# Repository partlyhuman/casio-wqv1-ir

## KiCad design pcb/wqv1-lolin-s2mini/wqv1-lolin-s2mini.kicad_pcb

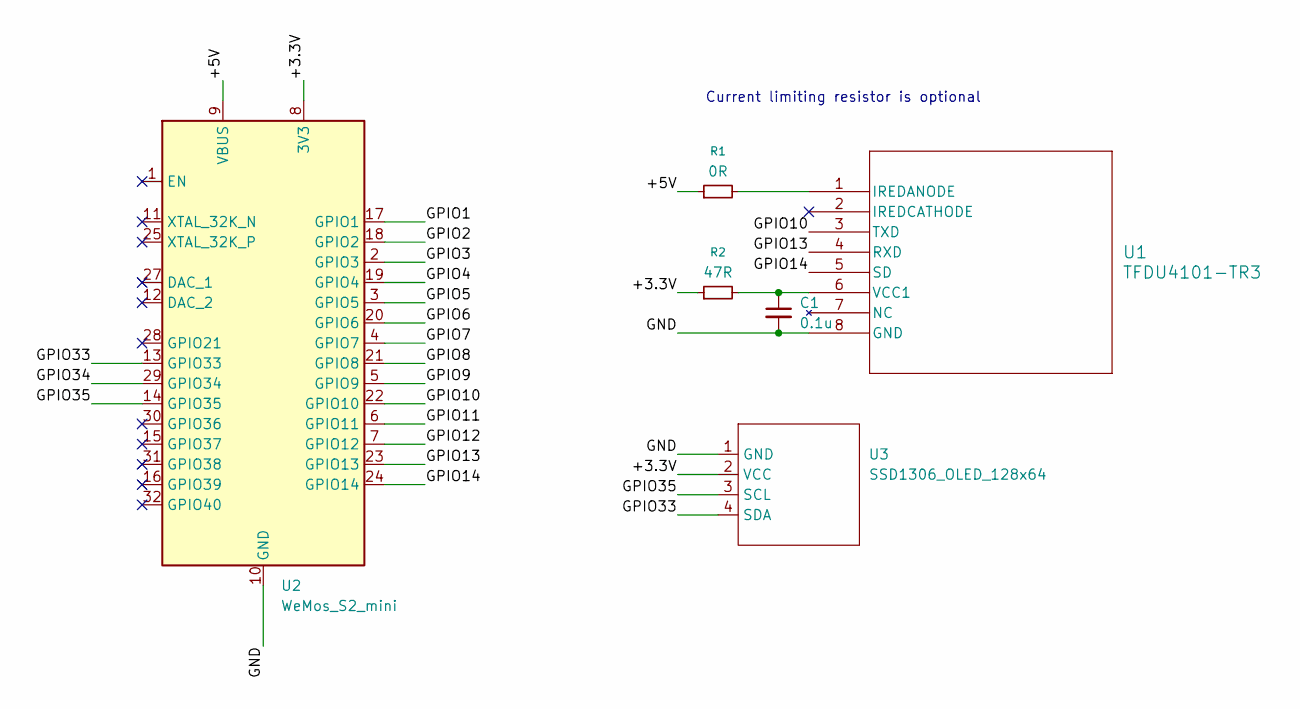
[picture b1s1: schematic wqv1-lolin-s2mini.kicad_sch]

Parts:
C1: 0.1u; C_0805_2012Metric_Pad1.18x1.45mm_HandSolder
R1: 0R; R_0805_2012Metric_Pad1.20x1.40mm_HandSolder
R2: 47R; R_0805_2012Metric_Pad1.20x1.40mm_HandSolder
U1: TFDU4101-TR3; SMT_101-TR3_VIS
U2: WeMos_S2_mini; WEMOS_S2_mini
U3: SSD1306_OLED_128x64; SSD1306

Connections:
/+3.3V: R2.1, U2.8 (3V3), U3.2 (VCC)
/+5V: R1.1, U2.9 (VBUS)
/GND: C1.2, U1.8 (GND), U2.10 (GND), U2.26 (GND), U3.1 (GND)
/GPIO1: U2.17 (GPIO1)
/GPIO2: U2.18 (GPIO2)
/GPIO3: U2.2 (GPIO3)
/GPIO4: U2.19 (GPIO4)
/GPIO5: U2.3 (GPIO5)
/GPIO6: U2.20 (GPIO6)
/GPIO7: U2.4 (GPIO7)
/GPIO8: U2.21 (GPIO8)
/GPIO9: U2.5 (GPIO9)
/GPIO10: U1.3 (TXD), U2.22 (GPIO10)
/GPIO11: U2.6 (GPIO11)
/GPIO12: U2.7 (GPIO12)
/GPIO13: U1.4 (RXD), U2.23 (GPIO13)
/GPIO14: U1.5 (SD), U2.24 (GPIO14)
/GPIO33: U2.13 (GPIO33), U3.4 (SDA)
/GPIO34: U2.29 (GPIO34)
/GPIO35: U2.14 (GPIO35), U3.3 (SCL)
unnamed: R1.2, U1.1 (IREDANODE)
unnamed: C1.1, R2.2, U1.6 (VCC1)

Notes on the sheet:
Current limiting resistor is optional

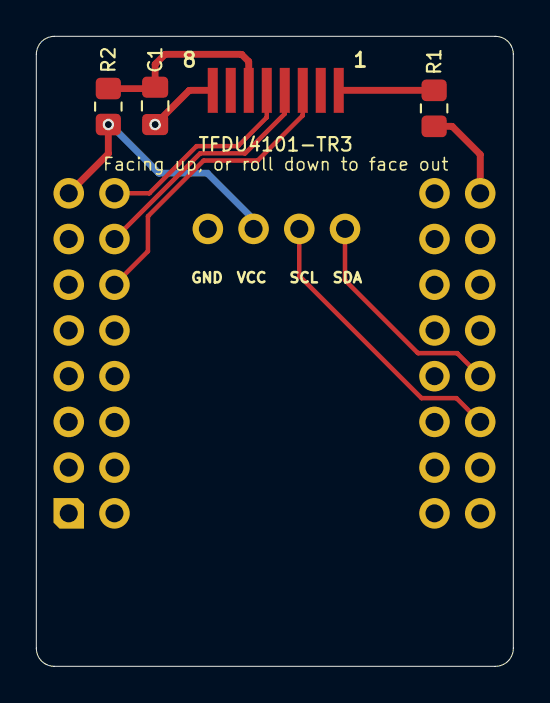
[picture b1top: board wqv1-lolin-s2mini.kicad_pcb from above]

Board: 2 copper layers, 26.5 x 35.0 mm, 6 parts (1 on the bottom side), 10 nets.

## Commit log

2026-01-18 First contact!
2026-01-18 Migrate to platformio
2026-01-18 Full handshake
2026-01-18 WIP before refactoring parseFrame to accept BOF-stripped
2026-01-18 Handshaking with read to EOF to avoid dropped messages
2026-01-19 Retrying, and upload preamble working
2026-01-19 Syncing?
2026-01-19 Actually loaded
2026-01-19 WIP RGBA
2026-01-19 Save to FatFs
2026-01-19 Fix FatFs
2026-01-19 Fixes
2026-01-19 Cleanup
2026-01-19 Reorg
2026-01-19 Init project of porting FATFSUSB from pico
2026-01-20 Figured out ejecting
2026-01-20 Use raw dump on FS instead of memory
2026-01-20 Many QOL including setting file creation time, fixed dates, metas
2026-01-20 Fix stupid esp logging not working
2026-01-20 PSRAM WIP, may roll back
2026-01-20 Also not working
2026-01-20 Good psram implementation, log levels
2026-01-21 Tiny change to psram initialization
2026-01-21 Stub out display
2026-01-22 WIP graphics
2026-01-22 Display WIP
2026-01-22 Displays
2026-01-22 Cleanups
2026-01-22 Remove template readmes
2026-01-22 Add notes on IRDA physical layer
2026-01-25 Start PCB projects with SMD IRDA breakout
2026-01-25 Abstract away some IRDA details
2026-01-25 New pins for PCB layout, tested
2026-01-25 PCB layout for LOLIN S2 based board
2026-01-25 Fix oled 3d linkage
2026-01-31 Small cleanups
2026-01-31 Docs and alternate meta formats
2026-01-31 Better naming schemes, configurable image format
2026-01-31 Save plain text title, when not blank only
